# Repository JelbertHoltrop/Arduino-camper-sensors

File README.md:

# Arduino-camper-sensors
An arduino mega based board to monitor air quality, current usage, waste water tank level.
The board uses a BME680 sensor for temperature, pressure, humidity and VOC gas sensor.
For current it uses a INA280 current sensor
For the water level it uses tree elektrodes. Between two poles in the bottom of the tank a reference is taken to measure the condustiveness of the fluid, waste water changes conductivity. The other elektrode is a long bare wire (goldplated) and is used to measure the fluid level. 

Many of the Arduino MEGA 2560 pins are avaliable on screw terminals on the edge of the board. 7 digital lines have a ULN2003 driver output.
On the board is a 240x320 touch screen shield attached for the gui.
The schematic and PCB files are made in Eagle. The pcb is simple and single sided.

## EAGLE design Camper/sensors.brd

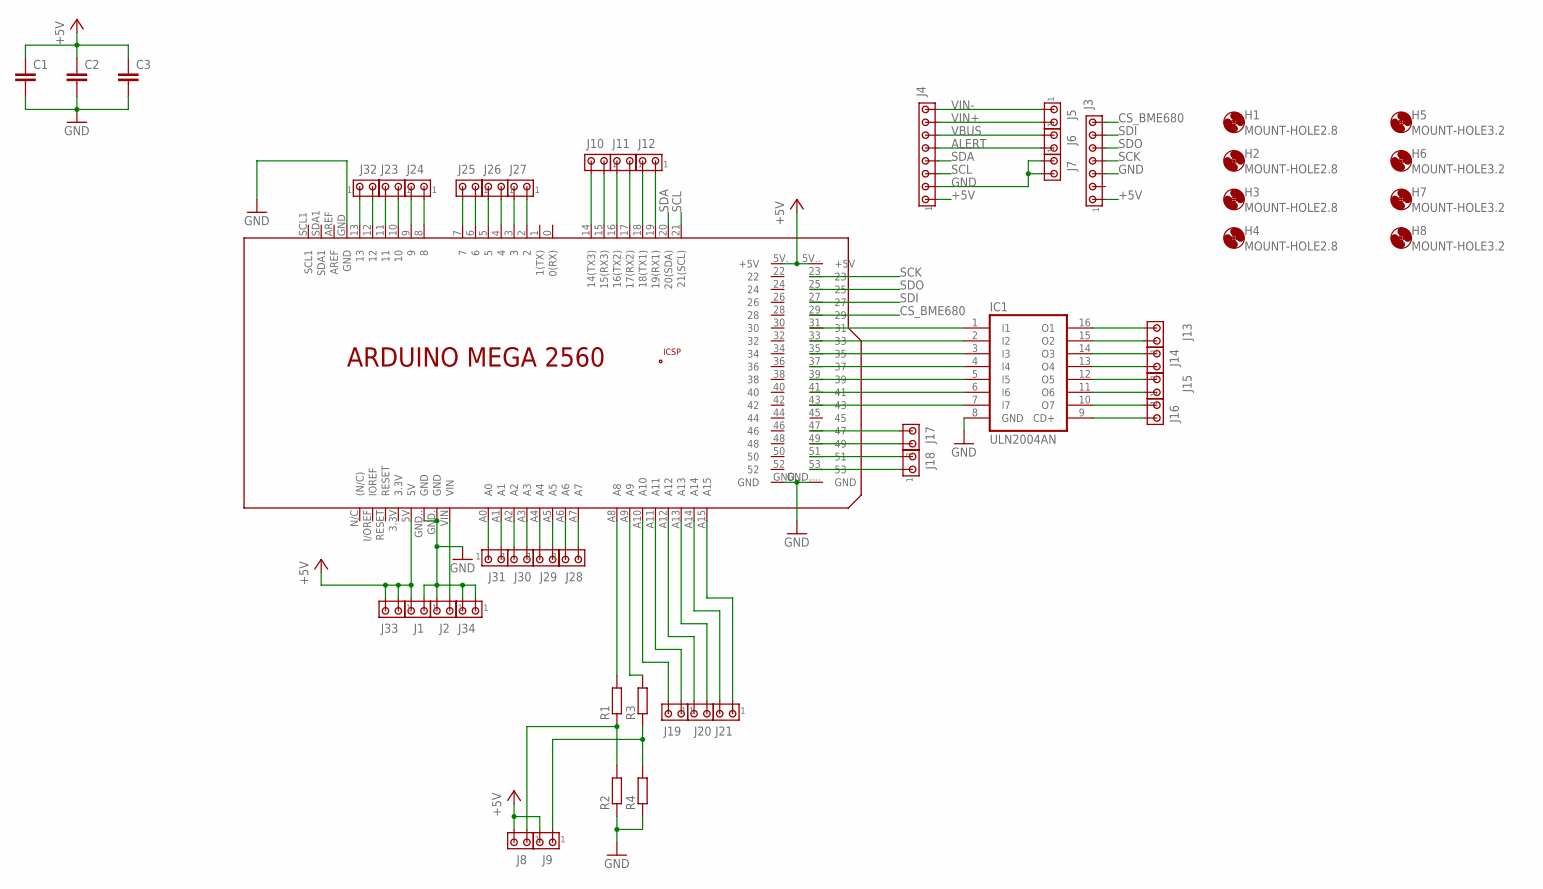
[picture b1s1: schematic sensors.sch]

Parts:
C1, C2, C3: C2,5-3; C2.5-3
H1, H2, H3, H4: MOUNT-HOLE2.8; 2,8
H5, H6, H7, H8: MOUNT-HOLE3.2; 3,2
IC1: ULN2004AN; DIL16
J1, J2, J5, J6, J7, J8, J9, J10, J11, J12, J13, J14, J15, J16, J17, J18, J19, J20, J21, J23, J24, J25, J26, J27, J28, J29, J30, J31, J32, J33, J34: SCREW-2
J3: MTA07-100; 10X07MTA
J4: MTA08-100; 10X08MTA
PCB1: ARDUINO_MEGA2560_NEW; ARDUINO_MEGA2560
R1, R2, R3, R4: R0207/10; 0207/10

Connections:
+5V: C1.1, C2.1, C3.1, J1.2, J3.1, J4.1, J8.2, J9.2, J33.1, J33.2, PCB1.5V, PCB1.5V. (+5V), PCB1.5V.. (+5V)
ALERT: J4.5, J6.2
CS_BME680: J3.7, PCB1.29
GND: C1.2, C2.2, C3.2, IC1.8 (GND), J1.1, J2.2, J3.3, J4.2, J7.1, J7.2, J34.1, J34.2, PCB1.GND, PCB1.GND. (GND), PCB1.GND.. (GND), PCB1.GND... (GND), PCB1.GND.... (GND), R2.1, R4.1
unnamed: J2.1, PCB1.VIN
unnamed: PCB1.A8, R1.2
unnamed: J8.1, R1.1, R2.2
unnamed: PCB1.A9, R3.2
unnamed: J9.1, R3.1, R4.2
unnamed: J19.2, PCB1.A10
unnamed: J19.1, PCB1.A11
unnamed: J20.1, PCB1.A12
unnamed: J20.2, PCB1.A13
unnamed: J21.2, PCB1.A14
unnamed: J21.1, PCB1.A15
unnamed: IC1.1 (I1), PCB1.31
unnamed: IC1.2 (I2), PCB1.33
unnamed: IC1.3 (I3), PCB1.35
unnamed: IC1.4 (I4), PCB1.37
unnamed: IC1.5 (I5), PCB1.39
unnamed: IC1.6 (I6), PCB1.41
unnamed: IC1.7 (I7), PCB1.43
unnamed: IC1.16 (O1), J13.2
unnamed: IC1.15 (O2), J13.1
unnamed: IC1.14 (O3), J14.2
unnamed: IC1.13 (O4), J14.1
unnamed: IC1.12 (O5), J15.2
unnamed: IC1.11 (O6), J15.1
unnamed: IC1.10 (O7), J16.1
unnamed: IC1.9 (CD+), J16.2
unnamed: J10.2, PCB1.14 (14(TX3))
unnamed: J10.1, PCB1.15 (15(RX3))
unnamed: J11.2, PCB1.16 (16(TX2))
unnamed: J11.1, PCB1.17 (17(RX2))
unnamed: J12.2, PCB1.18 (18(TX1))
unnamed: J12.1, PCB1.19 (19(RX1))
unnamed: J32.1, PCB1.13
unnamed: J32.2, PCB1.12
unnamed: J23.2, PCB1.11
unnamed: J23.1, PCB1.10
unnamed: J24.2, PCB1.9
unnamed: J24.1, PCB1.8
unnamed: J25.2, PCB1.7
unnamed: J25.1, PCB1.6
unnamed: J26.2, PCB1.5
unnamed: J26.1, PCB1.4
unnamed: J27.2, PCB1.3
unnamed: J27.1, PCB1.2
unnamed: J18.1, PCB1.53
unnamed: J18.2, PCB1.51
unnamed: J17.1, PCB1.49
unnamed: J17.2, PCB1.47
unnamed: J31.1, PCB1.A0
unnamed: J31.2, PCB1.A1
unnamed: J30.1, PCB1.A2
unnamed: J30.2, PCB1.A3
unnamed: J29.1, PCB1.A4
unnamed: J29.2, PCB1.A5
unnamed: J28.1, PCB1.A6
unnamed: J28.2, PCB1.A7
SCK: J3.4, PCB1.23
SCL: J4.3, PCB1.21 (21(SCL))
SDA: J4.4, PCB1.20 (20(SDA))
SDI: J3.6, PCB1.27
SDO: J3.5, PCB1.25
VBUS: J4.6, J6.1
VIN+: J4.7, J5.2
VIN-: J4.8, J5.1

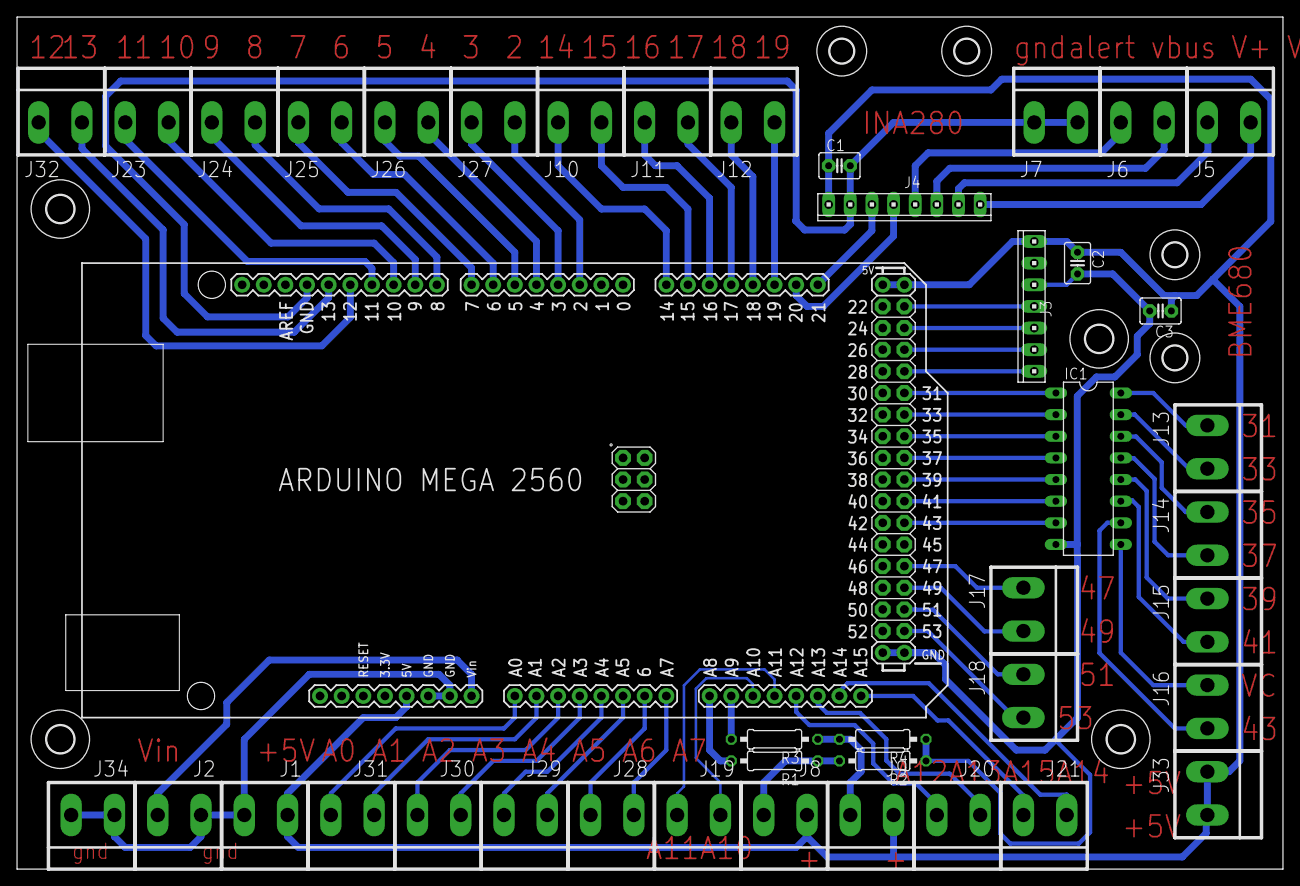
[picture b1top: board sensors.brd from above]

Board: 2 copper layers, 148.6 x 100.0 mm, 50 parts (0 on the bottom side), 68 nets.

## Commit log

2019-12-31 Update README.md
    added basic board info
2019-12-31 Add files via upload
    Eagle design files.
2019-12-31 Add files via upload
    first upload of arduino code.
    The sensor logs show the temprature drift of Rgas when the Adafruit libraries are used. The Adafruit libraries rely on BME680.c written by Bosch. The temprature drift is too big for any usefull usage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
    The libraries and platform.txt will be added later, after I read their license agreement.
